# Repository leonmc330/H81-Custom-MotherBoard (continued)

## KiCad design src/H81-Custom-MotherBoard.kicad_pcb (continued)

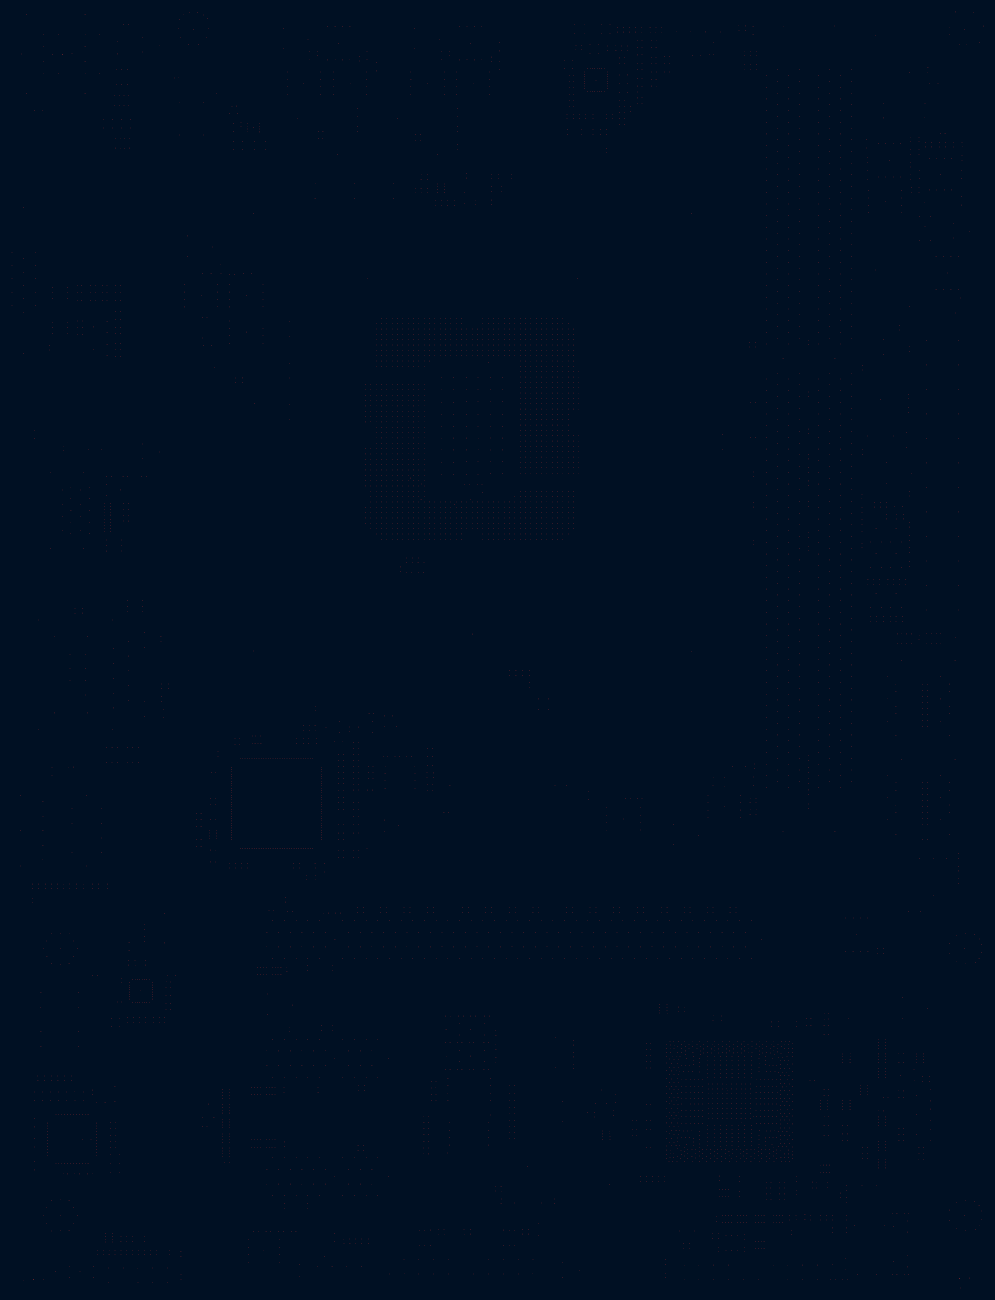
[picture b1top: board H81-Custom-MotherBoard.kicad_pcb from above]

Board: 4 copper layers, 930 parts (0 on the bottom side), 872 nets, no tracks yet.

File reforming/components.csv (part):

refdes,device,x,y,sizex,sizey,rotation
A,33/8P4R/4,-448000.000,15000.000,4920.000,5900.000,270.000
ATX,APW/2*12/BK/VA/SN/2SHK/PA66,-595325.000,499445.000,21650.000,218890.000,0.000
ATX_12V,APW/2*2/BK/P/4.2/SN/PA66,-92978.000,742876.000,27752.000,25497.000,90.000
AUDIO,A3RP/13P/BL,LI,PK/RA/D/1/B,-535.000,259571.000,47600.000,54300.000,90.000
BAT,BAT-SK/BK/P/S/D/SN,-302370.000,290000.000,0.000,78740.000,270.000
BC140,1u/4/X5R/6.3V/K,-465500.000,272000.000,0.000,3140.000,180.000
BC146,0.1u/4/X7R/16V/K/X,-573000.000,439500.000,0.000,3140.000,180.000
BC147,0.1u/4/X7R/16V/K,-573000.000,449000.000,0.000,3140.000,0.000
BC148,1u/4/X5R/6.3V/K,-573000.000,466000.000,0.000,3140.000,0.000
BC149,4.7u/6/X5R/6.3V/K,-565500.000,478500.000,0.000,5600.000,270.000
BC150,0.1u/4/X7R/16V/K,-573000.000,487000.000,0.000,3140.000,180.000
BC151,1u/4/X5R/6.3V/K,-572500.000,543500.000,0.000,3140.000,180.000
BC152,0.1u/4/X7R/16V/K,-572500.000,552500.000,0.000,3140.000,0.000
BC153,0.1u/4/X7R/16V/K,-573000.000,584500.000,0.000,3140.000,0.000
BC154,10u/6/X5R/6.3V/M,-440500.000,293000.000,0.000,5600.000,180.000
BC158,0.1u/4/X7R/16V/K,-579500.000,390000.000,0.000,3140.000,0.000
BC161,0.1u/4/X7R/16V/K/X,-293500.000,18000.000,0.000,3140.000,0.000
BC162,10u/6/X5R/6.3V/M/X,-544000.000,723000.000,0.000,5600.000,0.000
BC164,1n/4/X7R/50V/K,-333500.000,9500.000,0.000,3140.000,180.000
BC179,22u/8/X5R/6.3V/M,-223000.000,330000.000,0.000,7880.000,270.000
BC20,0.1u/4/X7R/16V/K,-117500.000,748500.000,0.000,3140.000,270.000
BC21,0.1u/4/X7R/16V/K,-78500.000,767500.000,0.000,3140.000,90.000
BC5,0.1u/4/X7R/16V/K/X,-2000.000,517500.000,0.000,3140.000,180.000
BC6,0.1u/4/X7R/16V/K/X,-33000.000,498500.000,0.000,3140.000,90.000
BC63,0.1u/4/X7R/16V/K/X,7000.000,585500.000,0.000,3140.000,0.000
BC67,0.01u/4/X7R/25V/K,-440000.000,-14000.000,0.000,3140.000,0.000
BC75,0.01u/4/X7R/25V/K,-462000.000,-23000.000,0.000,3140.000,0.000
BC78,0.01u/4/X7R/25V/K/X,-530500.000,-10000.000,0.000,3140.000,180.000
BC79,1u/4/X5R/6.3V/K,-209500.000,299000.000,0.000,3140.000,270.000
BC8,0.1u/4/X7R/16V/K/X,-44500.000,803500.000,0.000,3140.000,90.000
BC84,1u/4/X5R/6.3V/K,-249500.000,290500.000,0.000,3140.000,90.000
B_BIOS,MASK/32M/SPI/SO8/200mil/S/X,-276000.000,85000.000,28760.000,15000.000,0.000
C100,1u/4/X5R/6.3V/K,-465500.000,280000.000,0.000,3140.000,180.000
C104,1n/4/X7R/50V/K,-509000.000,22500.000,0.000,3140.000,90.000
C119,2.2n/4/X7R/50V/K,-544500.000,712000.000,0.000,3140.000,180.000
C12,0.1u/4/X7R/16V/K/X,-560000.000,402500.000,0.000,3140.000,0.000
C120,1u/6/X7R/16V/K/X,-589500.000,764000.000,0.000,5600.000,90.000
C121,0.1u/4/X7R/16V/K,-585500.000,773000.000,0.000,3140.000,0.000
C131,1u/6/X7R/16V/K,-608000.000,702500.000,0.000,5600.000,180.000
C132,1u/4/X5R/6.3V/K/X,-553000.000,427500.000,0.000,3140.000,180.000
C133,3.3n/4/X7R/50V/K,-574000.000,726000.000,0.000,3140.000,0.000
C134,22p/4/NPO/50V/J,-579500.000,717500.000,0.000,3140.000,0.000
C136,0.1u/4/X7R/16V/K,-579500.000,692000.000,0.000,3140.000,180.000
C143,0.1u/4/X7R/16V/K/X,-547000.000,402500.000,0.000,3140.000,0.000
C144,1n/4/X7R/50V/K/X,-564500.000,471500.000,0.000,3140.000,180.000
C16,0.01u/4/X7R/25V/K,-402000.000,800000.000,0.000,3140.000,180.000
C193,3.3n/4/X7R/50V/K,-597500.000,722500.000,0.000,3140.000,0.000
C31,100p/4/NPO/50V/J/X,-13500.000,599000.000,0.000,3140.000,90.000
C318,0.1u/4/X7R/16V/K,-549500.000,479500.000,0.000,3140.000,0.000
C32,100p/4/NPO/50V/J/X,-13500.000,594500.000,0.000,3140.000,270.000
C322,1u/6/X7R/16V/K,-467500.000,799500.000,0.000,5600.000,0.000
C323,0.1u/4/X7R/16V/K,-439500.000,783500.000,0.000,3140.000,90.000
C33,0.1u/4/X7R/16V/K/X,-13500.000,603500.000,0.000,3140.000,90.000
C34,10p/4/NPO/50V/J/X,-30000.000,617500.000,0.000,3140.000,270.000
C35,10p/4/NPO/50V/J/X,-30000.000,622500.000,0.000,3140.000,270.000
C36,10p/4/NPO/50V/J/X,-30000.000,627500.000,0.000,3140.000,270.000
C37,22p/4/NPO/50V/J/X,-13000.000,617500.000,0.000,3140.000,270.000
C38,22p/4/NPO/50V/J/X,-13000.000,622500.000,0.000,3140.000,270.000
C39,22p/4/NPO/50V/J/X,-13000.000,627500.000,0.000,3140.000,270.000
C40,0.1u/4/X7R/16V/K/X,-39000.000,610000.000,0.000,3140.000,90.000
C76,1n/4/X7R/50V/K,-235500.000,309500.000,0.000,3140.000,90.000
C80,1n/4/X7R/50V/K,-249500.000,303500.000,0.000,3140.000,90.000
C9,0.01u/4/X7R/25V/K,-203500.000,-17500.000,0.000,3140.000,0.000
CBC1,10u/6/X5R/6.3V/M,12000.000,80500.000,0.000,5600.000,0.000
CBC10,10u/6/X5R/6.3V/M,17500.000,33500.000,0.000,5600.000,0.000
CBC11,10u/6/X5R/6.3V/M,-4500.000,80500.000,0.000,5600.000,0.000
CBC12,10u/6/X5R/6.3V/M,17500.000,80500.000,0.000,5600.000,0.000
CBC19,180p/4/NPO/50V/J/X,-11000.000,222000.000,0.000,3140.000,0.000
CBC2,10u/6/X5R/6.3V/M,6500.000,80500.000,0.000,5600.000,0.000
CBC20,180p/4/NPO/50V/J/X,-32000.000,222000.000,0.000,3140.000,0.000
CBC23,180p/4/NPO/50V/J/X,-22000.000,222000.000,0.000,3140.000,0.000
CBC24,180p/4/NPO/50V/J/X,2000.000,222000.000,0.000,3140.000,0.000
CBC26,1n/4/X7R/50V/K,-41000.000,-25000.000,0.000,3140.000,180.000
CBC29,180p/4/NPO/50V/J/X,-65000.000,-25000.000,0.000,3140.000,180.000
CBC3,180p/4/NPO/50V/J/X,14500.000,222000.000,0.000,3140.000,0.000
CBC30,180p/4/NPO/50V/J/X,-53000.000,-25000.000,0.000,3140.000,180.000
CBC32,22p/4/NPO/50V/J/X,-35500.000,50000.000,0.000,3140.000,90.000
CBC34,10u/6/X5R/6.3V/M,-37000.000,35000.000,0.000,5600.000,270.000
CBC35,10u/6/X5R/6.3V/M,-37000.000,41000.000,0.000,5600.000,270.000
CBC36,180p/4/NPO/50V/J/X,-29000.000,-25000.000,0.000,3140.000,180.000
CBC37,180p/4/NPO/50V/J/X,-49000.000,-25000.000,0.000,3140.000,180.000
CBC38,0.1u/4/X7R/16V/K,-35500.000,62500.000,0.000,3140.000,90.000
CBC4,180p/4/NPO/50V/J/X,18500.000,222000.000,0.000,3140.000,0.000
CBC42,100p/4/NPO/50V/J/X,-3500.000,28000.000,0.000,3140.000,90.000
CBC43,100p/4/NPO/50V/J/X,-22000.000,83000.000,0.000,3140.000,0.000
CBC5,10u/6/X5R/6.3V/M,-10000.000,80500.000,0.000,5600.000,180.000
CBC6,10u/6/X5R/6.3V/M,-15500.000,80500.000,0.000,5600.000,180.000
CBC7,10u/6/X5R/6.3V/M,17500.000,49000.000,0.000,5600.000,180.000
CBC8,10u/6/X5R/6.3V/M,17500.000,62500.000,0.000,5600.000,0.000
CBC9,10u/6/X5R/6.3V/M,1000.000,80500.000,0.000,5600.000,0.000
CD1,AZ2225-01L/SOD323/X,-37000.000,82000.000,10.000,10240.000,0.000
CEC1,100uF/D/10V/6*5,13000.000,119000.000,0.000,10000.000,0.000
CEC2,100uF/D/10V/6*5,13000.000,145500.000,0.000,10000.000,0.000
CEC6,100uF/D/10V/6*5,-12500.000,119000.000,0.000,10000.000,0.000
CLR_CMOS,PH/1*2/BK/2.54/VA/D,-423000.000,-10500.000,0.000,10000.000,270.000
COUPON1,COUPON/X,-326000.000,348500.000,0.000,6800.000,270.000
COUPON2,COUPON/X,-326000.000,341500.000,0.000,6800.000,270.000
CQ2,BAT54A/SOT23/200mA,-1500.000,-38000.000,9260.000,7480.000,0.000
CQ4,BAT54A/SOT23/200mA,-18000.000,-38000.000,9260.000,7480.000,0.000
CR1,62/4,15000.000,92500.000,0.000,3140.000,0.000
CR11,62/4,-61000.000,-25000.000,0.000,3140.000,0.000
CR12,0/4/X,-57000.000,-25000.000,0.000,3140.000,0.000
CR13,62/4,-57000.000,-16000.000,0.000,3140.000,0.000
CR14,62/4,10500.000,92500.000,0.000,3140.000,0.000
CR16,8.2K/4,1500.000,92500.000,0.000,3140.000,0.000
CR17,62/4,6000.000,92500.000,0.000,3140.000,0.000
CR18,20K/4/1,10000.000,222000.000,0.000,3140.000,0.000
CR19,8.2K/4,-3000.000,92500.000,0.000,3140.000,0.000
CR20,5.1K/4/1,-2000.000,222000.000,0.000,3140.000,0.000
CR21,2.2/6,5500.000,299500.000,0.000,5600.000,0.000
CR22,62/4,-7500.000,92500.000,0.000,3140.000,0.000
CR23,10K/4/1,-26000.000,222000.000,0.000,3140.000,0.000
CR24,0/4/SHT/M/X,-81500.000,-41500.000,0.000,3140.000,0.000
CR34,20K/4/1,-11500.000,28000.000,0.000,3140.000,90.000
CR44,47/4/1,-41000.000,-16000.000,0.000,3140.000,180.000
CR49,0/4/SHT/M/X,-7500.000,302500.000,0.000,3140.000,270.000
CR5,62/4,18500.000,212500.000,0.000,3140.000,0.000
CR50,0/6/X,-18000.000,51000.000,0.000,5600.000,90.000
CR51,0/6/SHT/M/X,-27500.000,76000.000,0.000,5600.000,90.000
CR53,62/4,-33000.000,-25000.000,0.000,3140.000,0.000
CR54,22K/4,-37000.000,-25000.000,0.000,3140.000,180.000
CR55,20K/4/1,-45000.000,-25000.000,0.000,3140.000,180.000
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
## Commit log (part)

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2026-06-16 Initial commit: GA-H81M-S1 boardview to KiCad PCB toolchain
2026-06-16 Rename project to H81-Custom-MotherBoard
2026-06-18 first sch and pcb usable
